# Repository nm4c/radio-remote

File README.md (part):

# RadPi

RadPi puts a two-way radio on the web. A Raspberry Pi sits next to a radio, or carries its own
transceiver on a HAT, and anyone with a browser can listen, talk and run the radio from
anywhere, on a phone or a PC.

- **Remote operation:** receive audio and push-to-talk with low-latency WebRTC audio. Change
  channels or tune frequencies on a radio-style control head (a desk head on wide screens, a
  handheld on phones).
- **Two hardware options:**
  - The **RadPi Control HAT** drives an existing radio through its mic connector. It works with
    most land-mobile and UHF CB radios.
  - The **RadPi SA818 HAT** has a built-in 1 W UHF transceiver, with frequencies, CTCSS/DCS,
    a VFO and signal strength.
- **On-air tools:** selcall (send and decode), audio clips played to air, text to speech in a
  choice of voices (Australian male and female included), recording of the channel, voice
  effects, and TX tone control.
- **AI agent (optional):**
  - It transcribes the channel and recognises who's talking.
  - It learns new voices and names, and keeps notes on people.
  - It can banter on air in a persona and voice you choose, including an Australian one you
    train yourself.
  - The models can run on the Pi, on an AI HAT+ 2, or in the cloud.
- **Several operators, safely:** personal accounts with control or listen-only roles, an audit
  log, and one transmitter at a time. Transmit time-outs drop PTT if a browser goes quiet.
- **Open source:**
  - Software: GPL-3.0.
  - Hardware: CERN-OHL-S. Both HATs are KiCad projects with JLC-ready parts.
  - Mock radio and audio backends let you try it all on a laptop.

There are two hardware modes, set with `radio.type` in `config.yaml`:

| `radio.type` | Hardware | Channels |
|---|---|---|
| `buttons` (default) | An external radio through the **[RadPi Control HAT](pihat/)** (or hand-wired optos, [docs/HARDWARE.md](docs/HARDWARE.md)) | The radio's own channels, stepped with UP/DOWN presses |
| `sa818` | The **[RadPi SA818 HAT](sa818s-hat/)**: a 1 W UHF transceiver on the HAT, no external radio | A frequency/tone list in `config.yaml`, set over the module's serial port, plus direct frequency entry. Shows signal strength (RSSI) |

```
 Browser (phone / PC)                     Raspberry Pi                      Radio  
┌───────────────────┐   WebSocket    ┌──────────────────────┐  GPIO+opto  ┌──────────┐
│ PTT / CH▲▼ / list │◄──────────────►│ server (Python)      │────────────►│ PTT UP DN│
│ mic ─► Opus       │  JSON control  │  - PTT safety timers │  USB audio  │ MIC in   │
│ speaker ◄─ Opus   │◄══════════════►│  - channel tracking  │◄───────────►│ SPK out  │
│                   │ WebRTC (UDP)   │                      │             │          │
└───────────────────┘                └──────────────────────┘             └──────────┘
```

## Features

- Hold-to-talk button (mouse, touch or **Space** key). Mic audio streams to the radio.
- Low-latency audio over WebRTC (Opus over UDP), with automatic fallback to audio over the WebSocket.
  Settings shows the round trip and receive buffer.
- Receive audio with an RX level meter and a BUSY indicator.
- Channel ▲/▼ and jump-to-channel. The Pi presses UP/DOWN the right number of times.
- Channel names are set in config.
- Selcall: send 1-20 digit sequential tone calls from the radio face, and see calls heard on
  the channel. See [Selcall](#selcall).
- Audio clips: upload MP3s (or any audio the browser can play), pick one, and transmit it with
  the radio's Play key. See [Audio clips](#audio-clips).
- Say (off until you switch it on): type something, pick a voice, and the Pi speaks it on air.
  See [Say (text to speech)](#say-text-to-speech).
- Voice effects: Vader, Dalek, Demon, Robot, Giant, Female, Chipmunk and Ghost, switched on
  and off with the radio's P key. See [Voice effects](#voice-effects).
- Recording: the orange button records what the radio hears into 15-minute parts, which join the
  clip list. See [Recording](#recording).
- AI agent (off until you switch it on): transcribes the channel, recognises voices, learns new
  people, and can banter on air in a persona and voice of your choosing. See [AI agent](#ai-agent).
- A radio-style control head: a desk head on wide screens and a portrait handheld on phones.
  See [Control head](#control-head).
- With the RadPi SA818 HAT: frequencies, repeater offsets and CTCSS/DCS per channel, a VFO for any
  frequency in the band, and an RSSI bar on the display.
- Several operators can listen at once. Only one can transmit, and the others see who's on air.
- Personal accounts with **control** (everything) or **listen** (hear only) roles, an audit log of
  who did what, and login lockout. See [Accounts and security](#accounts-and-security).
- Safety features:
  - Server-side transmit time-out (`max_tx_seconds`).
  - PTT drops if the browser goes quiet (network loss, closed tab, phone locked).
  - PTT drops if the browser window loses focus.
  - No channel changes while transmitting.
  - GPIO pins stay low at boot.
- Mock GPIO and mock audio, so you can develop on a laptop without the radio.

## Try it on your laptop (no hardware)

```bash
cd radpi
python3 -m venv .venv && source .venv/bin/activate
pip install -r requirements.txt
cp config.example.yaml config.yaml
#  in config.yaml set: gpio.backend: mock, audio.backend: mock
python -m server.users -c config.yaml add me --role control    # asks for a password
python -m server -c config.yaml
```

Open <http://localhost:8080>. `localhost` counts as secure, so the mic works.
You'll hear a test tone burst every 10 s, and PTT/channel presses show in the server log.
Set `radio.type: sa818` to try the SA818S mode: the mock module answers commands and reports a wandering RSSI.
The mock audio also plays a received selcall (to `selcall.my_id`, or 12345) every 30 s.
Set `audio.backend: sounddevice` to use your laptop's own mic and speakers as a pretend radio.

## Control head

The top of the page is drawn as a radio. Wider screens get a desk control head and phones
(600 px and narrower) get a handheld. Both show the channel, name, frequency, TX with the
time-out countdown, BUSY, RSSI and signal bars.

| Control | Does |
|---|---|
| Channel knob (right on the desk head, the tall one on the handheld) | Picks a channel. The channel shows straight away in amber and is sent once you stop turning. |
| D-pad up / down | One channel up or down |
| Volume knob | Speaker volume, the same as the slider |
| Soft keys | Call (send the selcall number, or open the Selcall panel if none is entered), Play (transmit the picked audio clip; it shows Stop while a clip is on air), Chans (channel list, desk only), Tune (SA818) or Sync (button radios; desk only while clips are on), Setup (Settings) |
| Menu (handheld) | Settings |
| P (desk), P1 (handheld) | Switch the voice effect picked in the Voice effects panel on or off. The display shows FX while it's on. |
| Power (desk), held 1.5 s | Disconnect |
| Orange button (desk: top right; handheld: on top by the antenna) | Record: starts or stops recording received audio. While recording, any other control except the volume knob also stops it (and does nothing else). See [Recording](#recording). |

Knobs turn by dragging or with the mouse wheel. The handheld's top knobs roll with a swipe
across them. A focused knob also takes the arrow keys. PTT stays a separate button (or Space),
because neither head has one on its face.

The artwork is generated. Change `assets/control-head/build_template.py` (desk) or
`build_handheld.py` (handheld), then run them; they need `rsvg-convert` for the PNGs:

```bash
python3 assets/control-head/build_template.py && python3 assets/control-head/build_handheld.py
```

They write the app's SVGs and `radio_config.js` to `web/control-head/`, and PNG layers,
layout JSON and standalone test pages to `assets/control-head/output/`. The input handling,
`web/control-head/control_head.js`, is hand-written and shared by both templates.

## Selcall

Sequential tone calls of 1 to 20 digits, in the CCIR (100 ms tones), ZVEI-1 (70 ms) or EEA (40 ms)
standard (`selcall.standard`). Set `selcall.tone_ms` to run the standard's frequencies at another
tone length, such as CCIR at 50 ms. The decoder still hears calls with longer tones than that.
A digit that repeats the one before it is sent as the repeat tone.

- **Sending:** type the number in the Selcall panel, or tap a preset or an earlier call, then
  press the **Call** soft key. The Pi keys the radio, waits
  `tx_delay_ms` for the transmitter to come up, plays the tones into the mic line and unkeys.
  PTT is locked out while a call goes out, and a call can't start while anyone transmits.
- **Receiving:** the Pi watches the received audio for selcalls. Calls show on the head's bottom
  line, as a notice, and in the panel's list. A call to this station's `selcall.my_id` is
  highlighted and plays a short chime. Sequences shorter than `decode_min_digits` are ignored,
  so speech doesn't set it off. The decoder accepts tones up to about 2% off frequency.

The tones go out through the same audio path as voice, so `audio.tx_gain` and the sound card's
mixer apply (but not the TX tone control below, which would change their levels). Set `selcall.level` so the tones give normal deviation, about the same as speech.
Write selcall numbers in the config in quotes (`my_id: "01234"`), so leading zeros are kept.

## Audio clips

Recordings kept on the Pi and sent on air from the control head: a net opening, an ID, a test
message.

- **Adding:** in the Audio clips panel, press **Upload audio…** and choose one or more files.
  The browser converts each one itself (MP3, M4A, WAV, OGG: anything it can play), to mono at
  the wire rate, trims silence off the ends and uploads it. The Pi needs no audio codecs. Clips
  are limited to `clips.max_seconds` (60 s) and `clips.max_files` (50), and are shared by every
  operator.
- **Sending:** pick a clip, then press the **Play** soft key. The Pi keys the radio, waits
  `tx_delay_ms`, plays the clip and unkeys. While it plays, the key reads **Stop**, and any
  operator can press it to cut the clip off. PTT and selcalls are locked out meanwhile, and a clip
  can't start while anyone transmits. The transmit time-out still applies.
- **Level:** every clip is played with its peak at `clips.level`, so loud and quiet recordings
  go out alike. Like voice, it then goes through `audio.tx_gain` and the sound card's mixer.

The files are kept in `clips.dir` (`/opt/radpi/clips` on an install), as WAV files with
a `clips.json` list. `update.sh` leaves them alone. **Listen** next to a clip plays it in the
browser, where you can also save it. **Rename** gives a clip or recording a new name (up to
40 characters) for everyone; the file on the Pi keeps its ID, so nothing else changes.

## Recording

Press the orange button on the radio (or **Record** in the Audio clips panel) to record the
channel. Press it again to stop. While recording, pressing any other control except the
volume knob also stops it, and that press does nothing else.

- The display shows **REC**, and the panel shows the time so far and who started it.
- **Two modes**, picked with the tick box under the record bar before you start (the orange
  button uses the same setting; `record.mode` sets the default):
  - **Continuous:** everything, silence included.
  - **Only while the channel is active (VOX):** just the overs, back to back with a short gap
    (`vox_gap_ms`, 0.3 s) instead of the silence between them. "Active" means the busy line, or
    the RX level above `audio.busy_threshold_dbfs` without one, or us transmitting. Each over
    keeps `vox_preroll_ms` (0.5 s) from before it started, so the first syllable isn't lost, and
    recording runs on for `vox_hang_ms` (2 s) after it, so short pauses don't chop it up. The bar
    shows how much has been captured.
- **Both sides of the conversation.** While the radio is keyed its receiver is muted, so the
  recording takes what we send instead: voice (after any voice effect), selcalls and clips,
  copied from the sound card output in step with the received audio, at speech level whatever
  `audio.tx_gain` is. Turn this off with `record.include_tx: false`.
- Recordings are split into parts of `record.max_minutes` (15) of audio. When a part is full it
  joins the clip list as "Recording 08 Nov 14:05:00" and the next part starts with no gap.
  Stopping finishes the part in progress. In VOX mode a part is also finished after
  `vox_close_idle_minutes` (10) of quiet, so the overs so far appear in the list.
- It runs on the Pi, so it carries on with no one connected. It also carries on after a restart,
  and a part cut short by a power failure is recovered into the list.
- Storage: about 115 MB an hour. Once recordings pass `record.keep_mb` (2000 MB, about 17
  hours), the oldest are deleted. Uploaded clips are never deleted automatically. Recording
  stops, with a notice, if the disk gets down to `record.min_free_mb`.
- A recording can be played on air like any clip if it fits inside `ptt.max_tx_seconds`.
  Longer ones can't be picked, but you can still listen to and save them.

## Say (text to speech)

Type something in the **Say** panel, pick a voice and press **Say on air** (or Ctrl+Enter). The
Pi turns it into speech, keys the radio, waits `tts.tx_delay_ms` and speaks it, like a clip.
**Listen first** plays it in your own browser only, so you can check a voice or a tricky word
before it goes out. Off by default: set `tts.enabled: true` and list the voices in
`config.yaml` (see the `tts:` section of `config.example.yaml`).

- **Voices:** each one in `tts.voices` has a name for the list, a backend and that backend's
  voice. Mix them freely; the first is the default, and each browser remembers its last pick.

  | Backend | Australian voices | Notes |
  |---|---|---|
  | `azure` (Azure AI Speech) | `en-AU-NatashaNeural` (female), `en-AU-WilliamNeural` (male), and more | Natural sounding. Free tier. Needs `tts.azure.api_key` and `region` (e.g. `australiaeast`) |
  | `google` (Cloud Text-to-Speech) | `en-AU-Neural2-A`/`C` (female), `en-AU-Neural2-B`/`D` (male) | Needs `tts.google.api_key` |
  | `elevenlabs` | any Australian voice from its voice library | The most lifelike; small free tier. Needs `tts.elevenlabs.api_key` |
  | `piper` (offline, on the Pi) | none ready-made: [train your own](docs/voice/README.md) | British and American voices work out of the box. `sudo /opt/radpi/.venv/bin/pip install piper-tts`, then download a voice's `.onnx` and `.onnx.json` |

  The cloud voices need the internet and take about a second; Piper works with no connection.
- **Stopping:** while it speaks, any control operator can press **Stop**. PTT, clips and
  selcalls are locked out meanwhile, and Say can't start while anyone transmits. Text that takes
  longer than `ptt.max_tx_seconds` to say is refused, so split long messages up.
- **Level and words:** speech goes out with its peak at `tts.level`, through the TX tone
  control and `audio.tx_gain`. Add words it says wrong to `tts.pronounce`, spelled the way
  they should sound (`{"Wagga": "Wogga"}`).
- **Records:** each one is in the audit log (who, which voice, the text) and on the head's
  bottom line while it's on air. Listen-only accounts don't see the panel.
- **Keys:** the AI agent's voice (`bot.tts`) uses the same cloud keys if it doesn't have its own.

## Voice effects

Pick an effect in the **Voice effects** panel, then press **P** on the desk head (**P1** on the
handheld) to switch it on or off. The display shows **FX** while it's on, and the bottom line
briefly names the effect. Picking another effect while one is on switches straight to it, even
mid-transmission. Each operator has their own choice.

Every effect rebuilds the voice from scratch rather than just shifting it. The Pi splits your
speech into *what* is said (the shape of the mouth and throat, which carries the words) and *how*
your voice sounds (pitch, roughness, timbre), throws the second part away, and plays the first
through a new synthetic voice. Your own voice doesn't get through; only your timing and
articulation remain. Each effect then sets the new voice's size, pitch and colour:

| Effect | New voice |
|---|---|
| Vader | Bigger tract, 78 Hz, a metallic "mask" echo, light saturation |
| Dalek | Slightly small, near-monotone 95 Hz, through a 30 Hz ring modulator (as on the original) |
| Demon | Huge tract, 58 Hz with an octave-down growl, breath, distortion, a dark room |
| Robot | Monotone 100 Hz with a metallic comb |
| Giant | Big tract, 62 Hz, heavy bass, a large room |
| Female | Shorter tract, 205 Hz following your intonation, breathy |
| Chipmunk | Small tract, 330 Hz |
| Ghost | Whisper only (no pitch), with a long reverb |

The Pi applies the effect to your live voice only. Clips and selcalls go out unchanged, and the TX
tone control below still applies after the effect. Each effect is matched to the dry voice's
loudness and soft-limited, so deviation stays about the same. They add about 35 ms of delay.
Speak clearly: the new voice carries your articulation, and the strongest effects are harder to
understand on a weak signal. Each preset is a few lines in `server/voicefx.py` (warp = tract
size, f0 = pitch, keep = how much intonation survives) if you want to tune them.
Turn the feature off with `voice_fx: enabled: false`.

## AI agent

An optional agent that listens to the channel and can talk back. Turn it on with
`bot: enabled: true` in `config.yaml` (see the `bot:` section of `config.example.yaml`). An
**AI agent** panel then appears in the page. With `enabled: false` (the default) none of it loads
and the panel stays hidden.

Its Python packages (Whisper, the speaker model, Piper and PyTorch) come to well over a gigabyte,
so they're only installed if you ask:

- **New install:** `sudo ./deploy/install.sh --with-ai`.
- **Existing install:** `sudo ./deploy/update.sh --with-ai`. After that, plain `update.sh` keeps
  them up to date. Without the flag they're never downloaded.
- **Removing them:** `sudo ./deploy/update.sh --without-ai` rebuilds the venv without them.

For each over it:

1. Transcribes it: Whisper on the Pi's CPU (`faster_whisper`), or any OpenAI-compatible
   transcription server.
2. Works out who it was: a voiceprint (SpeechBrain ECAPA) compared with the people it knows.
   People you name are **known**. An unfamiliar voice is kept as **Caller N** and recognised next
   time, and becomes **acquainted** once it hears their name. Each person's voiceprint keeps a
   spread of their overs and matches on the closest few, so someone on two different radios is
   still one person. Callers that turn out to have the same voice are merged. When it isn't sure,
   it says so rather than guessing. A handle or name said on air beats the voice match.
   To tune the thresholds (`bot.speaker`): `python -m server.bot people --similar`.
3. Decides whether to say something: an LLM gets the persona, what it knows about the speaker
   (their notes), the last few overs and the new one. It runs on Ollama, on hailo-ollama on the
   AI HAT+ 2 (Pi 5), or on any OpenAI-compatible server. It can also add to the speaker's notes
   and pick up their name.
4. Speaks: Piper offline (your own Australian voice: [docs/voice/README.md](docs/voice/README.md)),
   or Azure, Google or ElevenLabs Australian voices over the internet. With `bot.tones` on, it
   picks a tone for each reply: normal, raised or shout. It also hears when someone is shouting,
   from the over's level against the channel's usual. A raised or shouted reply is faster, higher
   and louder (the cloud voices), and is driven into the mic like someone yelling (every voice).

The panel shows the live transcript with who said what and how sure it is. Control operators can:

- Switch its mode:
  - **Listen**: transcribe and identify only.
  - **Approve**: each reply waits for **Send** or **Discard**.
  - **Auto**: replies go on air by themselves.
- Stop it mid-sentence.
- Name a voice from any over (**Name…**).
- Rename, merge or forget people.

Behaviour comes from the config and the persona prompt, not the code:

- The persona: `bot.persona`. Built in: `banter` (friendly, the default) and `cb` (foul-mouthed, gives as good as it gets), in `server/bot/prompts/`; or a path to your own file.
- When it speaks: `reply_policy` is `llm`, `always` or `addressed`.
- Rate limits: `max_replies_per_hour`, `min_reply_gap_s`. They're off by default.
- What it learns: `learn_anonymous`, `learn_notes`.

The code fixes only the radio mechanics:

- It waits for the channel to be quiet (`reply_gap_ms`) and never keys over anyone.
- Replies are capped at `max_reply_s`, and the server's transmit time-out still applies.
- Any operator can stop it.

Its transmissions go in the audit log as `kind: bot`.

Everything it learns is plain files in `bot.dir`. These can be read, edited and deleted directly:

- `people/people.json`: who it knows.
- `people/<id>.md`: notes on each person.
- `people/<id>.npy`: voiceprints.

The research log is `bot.dir/log/<date>.jsonl`. It records every over: transcript, speaker match
and score, and timings. It records every LLM decision, including the raw answer and silences, and
what happened to each reply (sent, dropped and why, discarded, stopped). With `keep_audio` it also
keeps each over's audio. `retention_days` prunes old logs and audio.

Try it without a radio, on recordings:

```bash
python -m server.bot -c config.yaml enrol --name Dave dave-1.wav dave-2.wav   # seed a known voice
python -m server.bot -c config.yaml replay overs/*.wav          # each file is one over
python -m server.bot -c config.yaml replay --split evening.wav  # cut a long recording into overs
python -m server.bot -c config.yaml people                      # who it knows
```

`replay` runs the full pipeline and writes the replies it would have sent as WAVs (`--out`). Use
`--dir` to keep test runs out of the live agent's memory.

Rough timings on a Pi 5:

| Step | Time |
|---|---|
| Whisper `base.en` | a few seconds per over |
| Speaker match | well under a second |
| A 1.5B model on the AI HAT+ 2 | a few seconds |
| Piper | faster than real time |

So expect roughly 4–10 s from un-key to reply. Mock backends (`backend: mock` for each) let you
try the panel on a laptop.

## TX tone control

Transmitted voice and clips pass through a bass and treble shelf on the Pi, because phone and
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
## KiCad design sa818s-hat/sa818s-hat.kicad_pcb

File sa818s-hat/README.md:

# RadPi SA818 HAT

A Raspberry Pi 4 HAT with a **built-in 1 W UHF FM transceiver**: no external radio. A NiceRF SA818S-U
module (400–480 MHz) is controlled by the Pi over a serial port, with audio through the same
TLV320AIC3104 I2S codec as the [RadPi Control HAT](../pihat/). It's meant for licensed amateur or
experimental use.

| Block | What's on the board |
|---|---|
| Transceiver | SA818S-U, frequency, CTCSS/DCS and squelch set over UART (9600 8N1, GPIO14/15) |
| Harmonic filter | 7th-order low-pass tuned for 400–480 MHz (−3 dB at about 550 MHz): 0.45–0.65 dB loss across the band, 0.62 dB at 477 MHz, return loss better than 22 dB, about −57 dB at the 2nd harmonic of 477 MHz (simulated with the parts' Q, ESR, self-resonance and tolerances). Murata LQW18AN 18 nH 2 % wirewound inductors (lowest-resistance 0603 version), Murata GJM high-Q C0G capacitors (5.6 pF ±0.1 pF, 13 pF ±2 %), all 0402 |
| Antenna | Vertical through-hole SMA (Amphenol 132134-11 footprint: any vertical THT SMA jack with legs on a 5.08 mm square), hand-soldered (not fitted by JLC), right at the filter output; the antenna screws on through the top of the case. Footprint for a 220 nH static-bleed inductor (L6, not fitted) |
| Control | PTT via MOSFET (boots in receive), high/low power via open-drain MOSFET, power-down on GPIO27, busy from the module's AudioON on GPIO23 |
| Audio | Codec headphone out → −30 dB → MIC_IN; AF_OUT → −6 dB → codec input. Direct, no transformers (shared ground). C0G coupling capacitors and thin-film resistors |
| Power | **From the Pi's 5 V only** (power the Pi from its USB-C socket; no input of its own). Module: TPS7A94 ultra-low-noise LDO at 4.2 V, then a ferrite + polymer-tantalum pi-filter. Codec: TPS7A2033 (3.3 V analog) and TPS7A2018 (1.8 V digital core), each from 5 V so the digital core's current pulses stay off the analog rail |
| ID EEPROM | AT24C32D, write-protected by default (R3 pull-up); ground test point TP1 while writing it |

## Schematic

The whole circuit on one page (click to open it full size; part and net names are searchable). Labels
with the same name are connected. Regenerate it with `python3 tools/overview.py` after changing the
schematic.

## GPIO use

| Pin | GPIO | Function |
|---|---|---|
| 8 / 10 | 14 / 15 | UART TX / RX to the module |
| 11 | 17 | PTT (high = transmit) |
| 13 | 27 | Module power: high = on, low = sleep (pulled low at boot) |
| 15 | 22 | Low power: high = 0.5 W, low = 1 W |
| 16 | 23 | Busy: low = signal present (`busy_pin: 23`, `busy_pull_up: true`) |
| 12, 35, 38, 40 / 3, 5 / 37 | 18–21 / 2, 3 / 26 | I2S, I2C and reset for the codec |

The Pi 4's main UART is normally used by Bluetooth. Add `dtoverlay=disable-bt` (or `miniuart-bt`) to
`/boot/firmware/config.txt`.

## Files

| File | |
|---|---|
| `sa818s-hat.kicad_pro` / `.kicad_sch` / `.kicad_pcb` | KiCad project (from KiCad's built-in Raspberry Pi HAT template) |
| `sa818s-hat.kicad_sym`, `sa818s-hat.pretty/` | Project library: SA818S symbol and footprint, codec symbol |
| `docs/schematic.svg` | The full schematic on one page (made by `tools/overview.py`) |
| `tools/` | Generator for the sheets (`build.py`) and netlist check (`verify.py`). Uses the shared code in `../kicadgen/` and the power and codec sheets from `../pihat/tools/kicad/` |

## Before layout

- **Power budget** (official 5.1 V 3 A Pi supply): Pi 4 up to about 1.3 A, module 0.65–0.75 A on transmit at
  high power, codec and the rest under 50 mA: about 2.1 A. Power-hungry USB devices on the Pi can tip it over.
- **SA818S footprint:** pad positions agree between two independent footprints (one derived from LCSC/EasyEDA)
  and the datasheet drawing. Print it 1:1 and check a module against it before ordering.
- **RF layout:** 50 Ω grounded coplanar waveguide from the module's ANT pad through the filter to the SMA,
  short and straight, with ground vias beside every filter capacitor and a solid ground plane under the module.
  Leave room for a shield can over the module and filter.
- **Supplies:** place C38/C39/C40/C45 at the module's VBAT pad (C45, 100 pF, nearest the pin). U7 (TPS7A94):
  C31/C32 at IN and C33/C35 at OUT with their grounds together at U7's GND pin, no vias in between; SNS
  (pin 8) Kelvin to C33; thermal pad to a large ground area (about 0.6 W while transmitting).
- **12 MHz codec clock:** its 37th–39th harmonics are 444, 456 and 468 MHz (and 432 MHz). Keep Y1 and the
  MCLK trace (R16, 100 Ω to slow the edges) away from the module and the RF path, with ground pour around them.
  Avoid channels within a few kHz of those frequencies. If they're audible on receive, fit the shield can.
- **L6 (not fitted):** before fitting, measure U6 pin 12 for DC with the module receiving and transmitting into a
  dummy load. Fit it only if it reads 0 V.
- **Check harmonics** on a spectrum analyser after the first build, before connecting an antenna.
- **Frequency range:** the module covers 400–480 MHz (the SA818S-CE is the same module with CE-RED certification). NiceRF only promises power flat within 1 dB up to 470 MHz, so measure the output at your frequency.

## Software

Set `radio.type: sa818` in `config.yaml` (see `config.example.yaml`):

- `channel.list`: name, frequency, optional `tx_freq` for repeaters, `tone` (CTCSS Hz or DCS `D023N`),
  and per-channel bandwidth, squelch or low power.
- The web app shows the frequency and tones, an RSSI bar, and a box to tune any frequency in `sa818.band` (the VFO).
- At start-up the server wakes the module (PD), sets volume, audio filters and tail tone, then the channel.
  If the module stops answering, operators see the error, PTT is refused, and the server retries every 5 s.
- `gpio.busy_pin: 23` uses the module's AudioON as the BUSY indicator.
- RSSI is the module's raw 0–255 reading in 1 dB steps. Set `sa818.rssi_offset_db` after checking it against a
  known signal to show dBm.

Pi 4 set-up: `dtoverlay=disable-bt` in `/boot/firmware/config.txt`, the serial console off and the serial
hardware on (`raspi-config` → Interface Options → Serial Port), then reboot. The installer adds the service user
to `dialout` for `/dev/serial0`.

## Licence

Hardware: CERN-OHL-S v2 (see [`LICENSE`](LICENSE)). The generator scripts are GPL-3.0-or-later (see the
repository root).

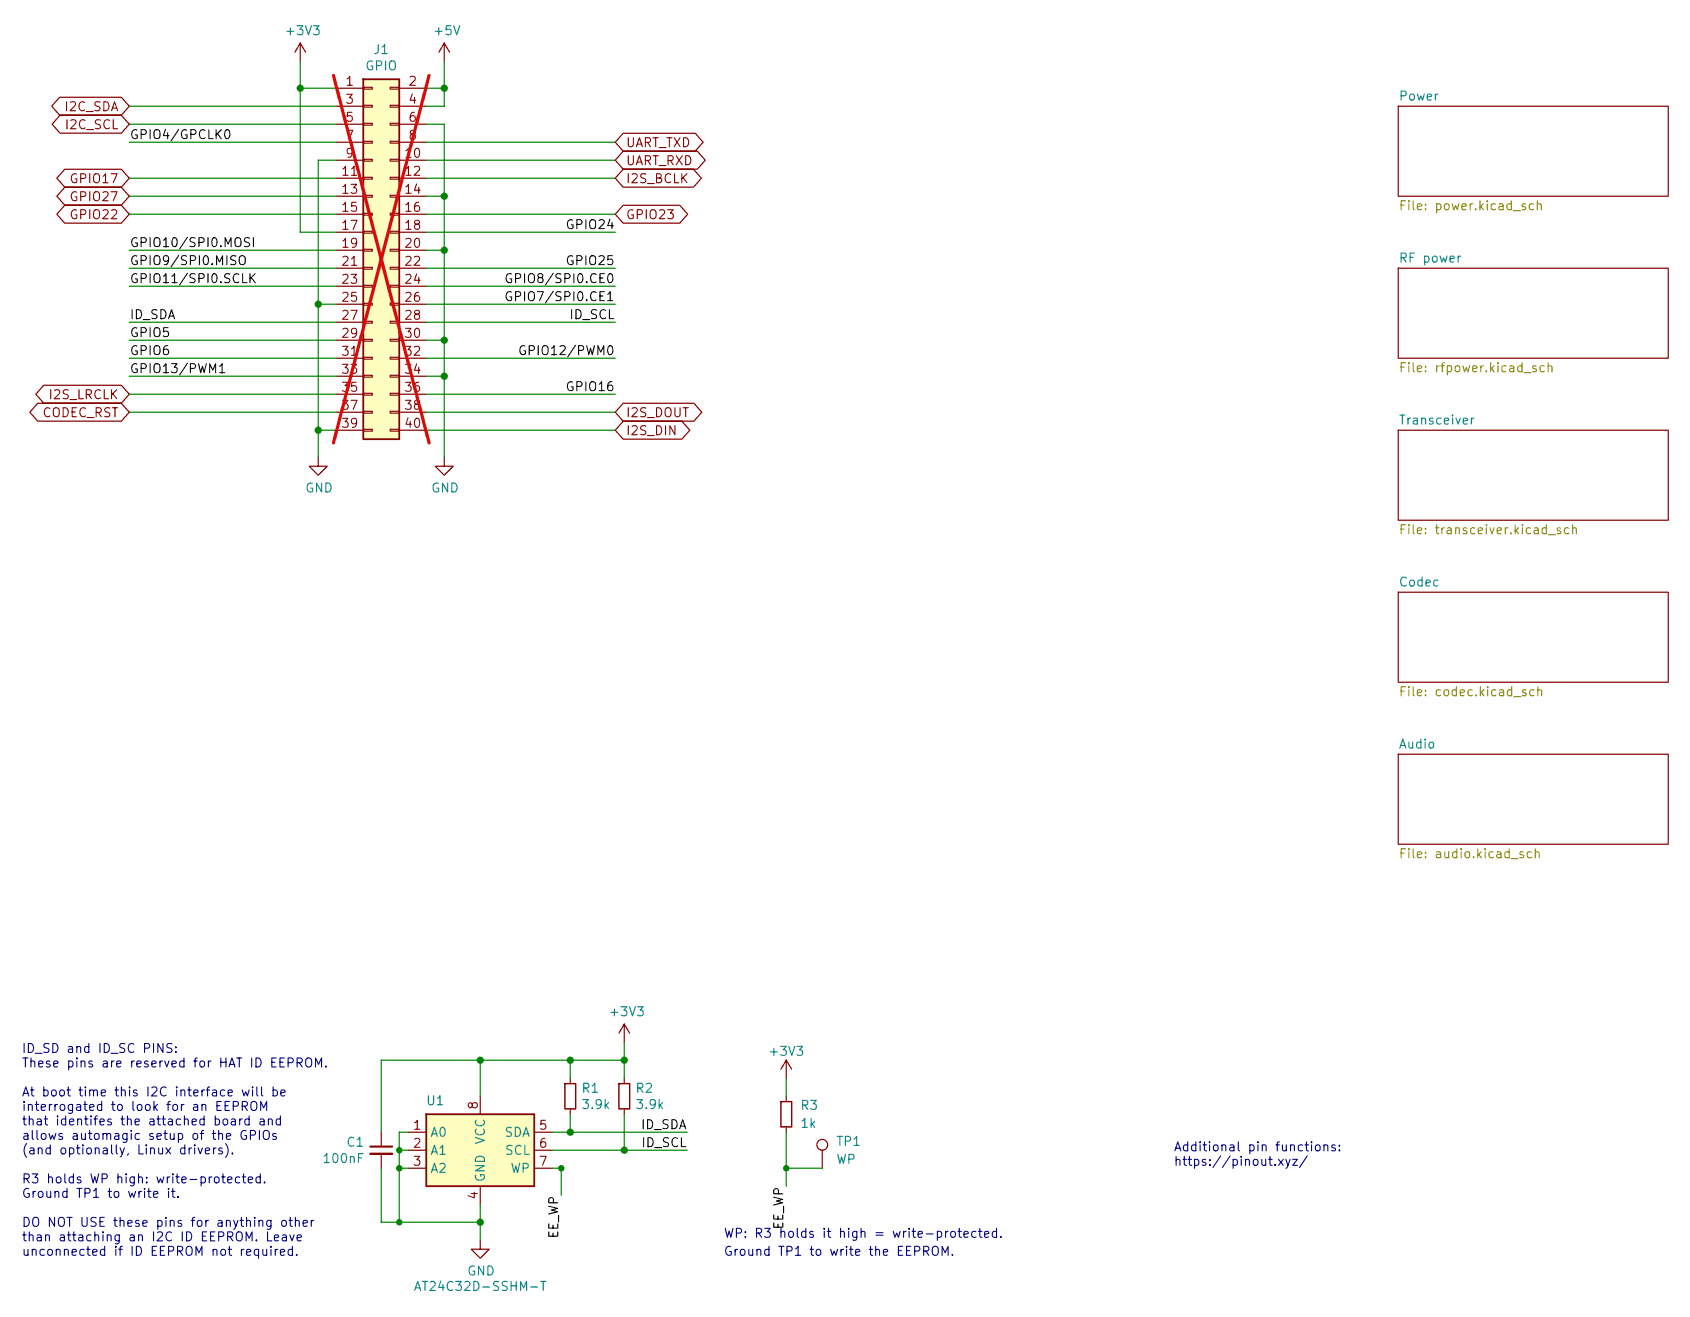
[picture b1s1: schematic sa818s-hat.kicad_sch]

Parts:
C1: 100nF; C_0603_1608Metric; LCSC C14663
J1: GPIO; PinSocket_2x20_P2.54mm_Vertical; LCSC C2977589; not fitted
R1, R2: 3.9k; R_0603_1608Metric; LCSC C23018
R3: 1k; R_0603_1608Metric; LCSC C21190
TP1: WP; TestPoint_Pad_D1.5mm
U1: AT24C32D-SSHM-T; SOIC-8_3.9x4.9mm_P1.27mm; LCSC C60583

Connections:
+3V3: C1.1, J1.1, J1.17, R1.1, R2.1, R3.1, U1.8 (VCC); also elsewhere on the board
+5V: J1.2, J1.4; also elsewhere on the board
/EE_WP: R3.2, TP1.1 (1_1), U1.7 (WP)
/GPIO4/GPCLK0: J1.7
/GPIO5: J1.29
/GPIO6: J1.31
/GPIO7/SPI0.CE1: J1.26
/GPIO8/SPI0.CE0: J1.24
/GPIO9/SPI0.MISO: J1.21
/GPIO10/SPI0.MOSI: J1.19
/GPIO11/SPI0.SCLK: J1.23
/GPIO12/PWM0: J1.32
/GPIO13/PWM1: J1.33
/GPIO16: J1.36
/GPIO24: J1.18
/GPIO25: J1.22
/ID_SCL: J1.28, R2.2, U1.6 (SCL)
/ID_SDA: J1.27, R1.2, U1.5 (SDA)
CODEC_RST: J1.37; also elsewhere on the board
GND: C1.2, J1.6, J1.9, J1.14, J1.20, J1.25, J1.30, J1.34, J1.39, U1.1 (A0), U1.2 (A1), U1.3 (A2), U1.4 (GND); also elsewhere on the board
GPIO17: J1.11; also elsewhere on the board
GPIO22: J1.15; also elsewhere on the board
GPIO23: J1.16; also elsewhere on the board
GPIO27: J1.13; also elsewhere on the board
I2C_SCL: J1.5; also elsewhere on the board
I2C_SDA: J1.3; also elsewhere on the board
I2S_BCLK: J1.12; also elsewhere on the board
I2S_DIN: J1.40; also elsewhere on the board
I2S_DOUT: J1.38; also elsewhere on the board
I2S_LRCLK: J1.35; also elsewhere on the board
UART_RXD: J1.10; also elsewhere on the board
UART_TXD: J1.8; also elsewhere on the board

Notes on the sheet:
Additional pin functions: https://pinout.xyz/
ID_SD and ID_SC PINS: These pins are reserved for HAT ID EEPROM. At boot time this I2C interface will be interrogated to look for an EEPROM that identifes the attached board and allows automagic setup of the GPIOs (and optionally, Linux drivers). R3 holds WP high: write-protected. Ground TP1 to wri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
WP: R3 holds it high = write-protected.
Ground TP1 to write the EEPROM.

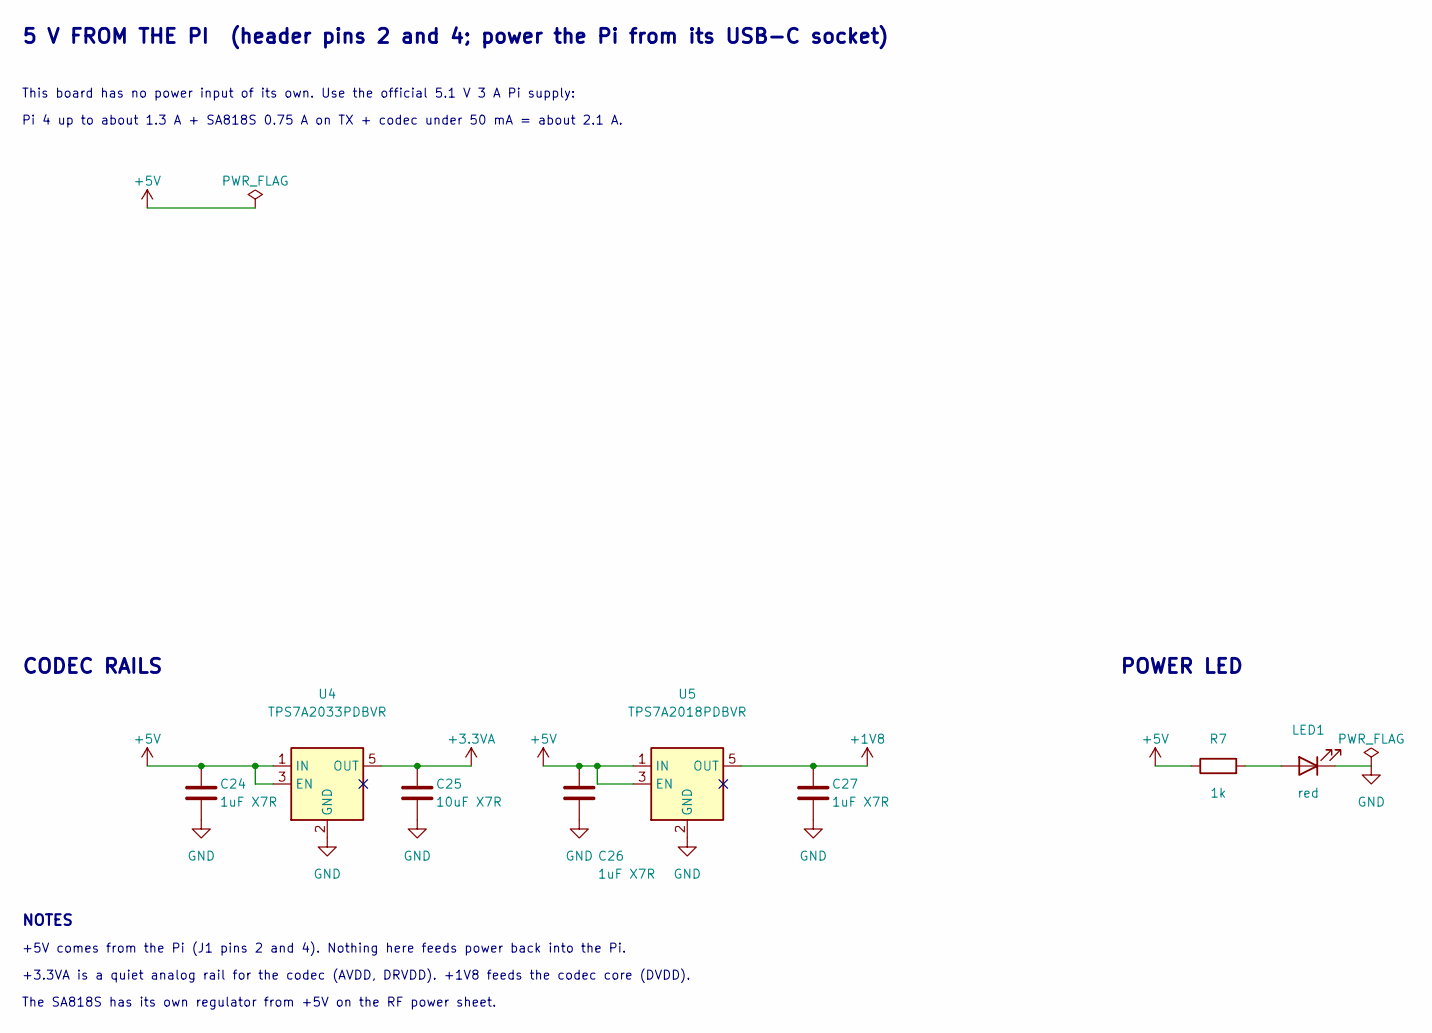
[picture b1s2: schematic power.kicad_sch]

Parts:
C24, C26, C27: 1uF X7R; C_0603_1608Metric; LCSC C29936
C25: 10uF X7R; C_0805_2012Metric; LCSC C95841
LED1: red; LED_0603_1608Metric; LCSC C2286
R7: 1k; R_0603_1608Metric; LCSC C21190
U4: TPS7A2033PDBVR; SOT-23-5; LCSC C2862740
U5: TPS7A2018PDBVR; SOT-23-5; LCSC C963430

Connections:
+1V8: C27.1, U5.5 (OUT); also elsewhere on the board
+3.3VA: C25.1, U4.5 (OUT); also elsewhere on the board
+5V: C24.1, C26.1, R7.1, U4.1 (IN), U4.3 (EN), U5.1 (IN), U5.3 (EN); also elsewhere on the board
GND: C24.2, C25.2, C26.2, C27.2, LED1.1 (K), U4.2 (GND), U5.2 (GND); also elsewhere on the board
unnamed: LED1.2 (A), R7.2

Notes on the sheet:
5 V FROM THE PI (header pins 2 and 4; power the Pi from its USB-C socket)
This board has no power input of its own. Use the official 5.1 V 3 A Pi supply:
Pi 4 up to about 1.3 A + SA818S 0.75 A on TX + codec under 50 mA = about 2.1 A.
CODEC RAILS
POWER LED
NOTES
+5V comes from the Pi (J1 pins 2 and 4). Nothing here feeds power back into the Pi.
+3.3VA is a quiet analog rail for the codec (AVDD, DRVDD). +1V8 feeds the codec core (DVDD).
The SA818S has its own regulator from +5V on the RF power sheet.

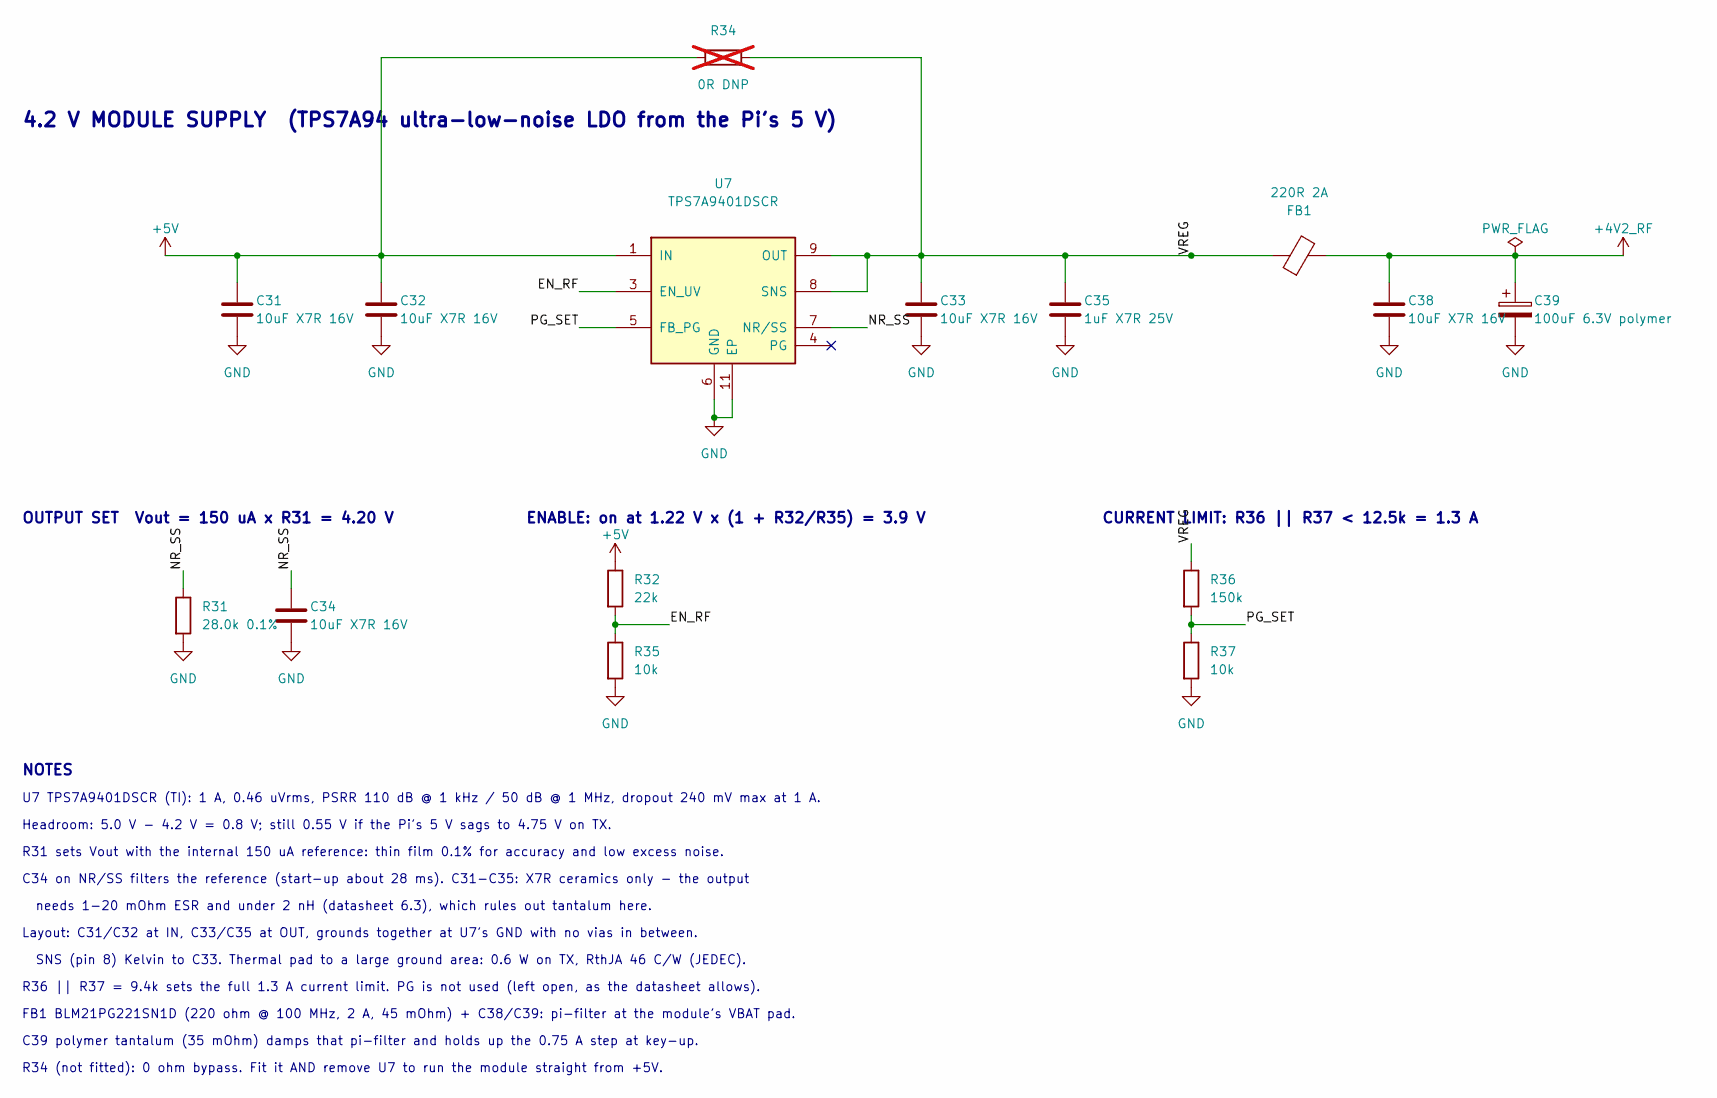
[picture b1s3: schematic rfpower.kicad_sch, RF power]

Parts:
C31, C32, C33, C34, C38: 10uF X7R 16V; C_0805_2012Metric; LCSC C95841
C35: 1uF X7R 25V; C_0603_1608Metric; LCSC C29936
C39: 100uF 6.3V polymer; CP_EIA-3528-21_Kemet-B; MPN Panasonic 6TPE100MAZB (POSCAP, 35 mOhm); LCSC C79109
FB1: 220R 2A; L_0805_2012Metric; LCSC C85840
R31: 28.0k 0.1%; R_0603_1608Metric; MPN FH TD03G2802BT (thin film, 0.1%, 25 ppm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; LCSC C667083
R32: 22k; R_0603_1608Metric; LCSC C31850
R34: 0R DNP; R_1206_3216Metric; not fitted
R35, R37: 10k; R_0603_1608Metric; LCSC C25804
R36: 150k; R_0603_1608Metric; LCSC C22807
U7: TPS7A9401DSCR; Texas_DSC0010J_ThermalVias; LCSC C5220127

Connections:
+4V2_RF: C38.1, C39.1, FB1.2; also elsewhere on the board
+5V: C31.1, C32.1, R32.1, R34.1, U7.1 (IN), U7.2 (IN); also elsewhere on the board
/RF power/EN_RF: R32.2, R35.1, U7.3 (EN_UV)
/RF power/NR_SS: C34.1, R31.1, U7.7 (NR/SS)
/RF power/PG_SET: R36.2, R37.1, U7.5 (FB_PG)
/RF power/VREG: C33.1, C35.1, FB1.1, R34.2, R36.1, U7.8 (SNS), U7.9 (OUT), U7.10 (OUT)
GND: C31.2, C32.2, C33.2, C34.2, C35.2, C38.2, C39.2, R31.2, R35.2, R37.2, U7.6 (GND), U7.11 (EP); also elsewhere on the board

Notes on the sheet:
4.2 V MODULE SUPPLY (TPS7A94 ultra-low-noise LDO from the Pi's 5 V)
OUTPUT SET Vout = 150 uA x R31 = 4.20 V
ENABLE: on at 1.22 V x (1 + R32/R35) = 3.9 V
CURRENT LIMIT: R36 || R37 < 12.5k = 1.3 A
NOTES
U7 TPS7A9401DSCR (TI): 1 A, 0.46 uVrms, PSRR 110 dB @ 1 kHz / 50 dB @ 1 MHz, dropout 240 mV max at 1 A.
Headroom: 5.0 V - 4.2 V = 0.8 V; still 0.55 V if the Pi's 5 V sags to 4.75 V on TX.
R31 sets Vout with the internal 150 uA reference: thin film 0.1% for accuracy and low excess noise.
C34 on NR/SS filters the reference (start-up about 28 ms). C31-C35: X7R ceramics only - the output
needs 1-20 mOhm ESR and under 2 nH (datasheet 6.3), which rules out tantalum here.
Layout: C31/C32 at IN, C33/C35 at OUT, grounds together at U7's GND with no vias in between.
SNS (pin 8) Kelvin to C33. Thermal pad to a large ground area: 0.6 W on TX, RthJA 46 C/W (JEDEC).
R36 || R37 = 9.4k sets the full 1.3 A current limit. PG is not used (left open, as the datasheet allows).
FB1 BLM21PG221SN1D (220 ohm @ 100 MHz, 2 A, 45 mOhm) + C38/C39: pi-filter at the module's VBAT pad.
C39 polymer tantalum (35 mOhm) damps that pi-filter and holds up the 0.75 A step at key-up.
R34 (not fitted): 0 ohm bypass. Fit it AND remove U7 to run the module straight from +5V.

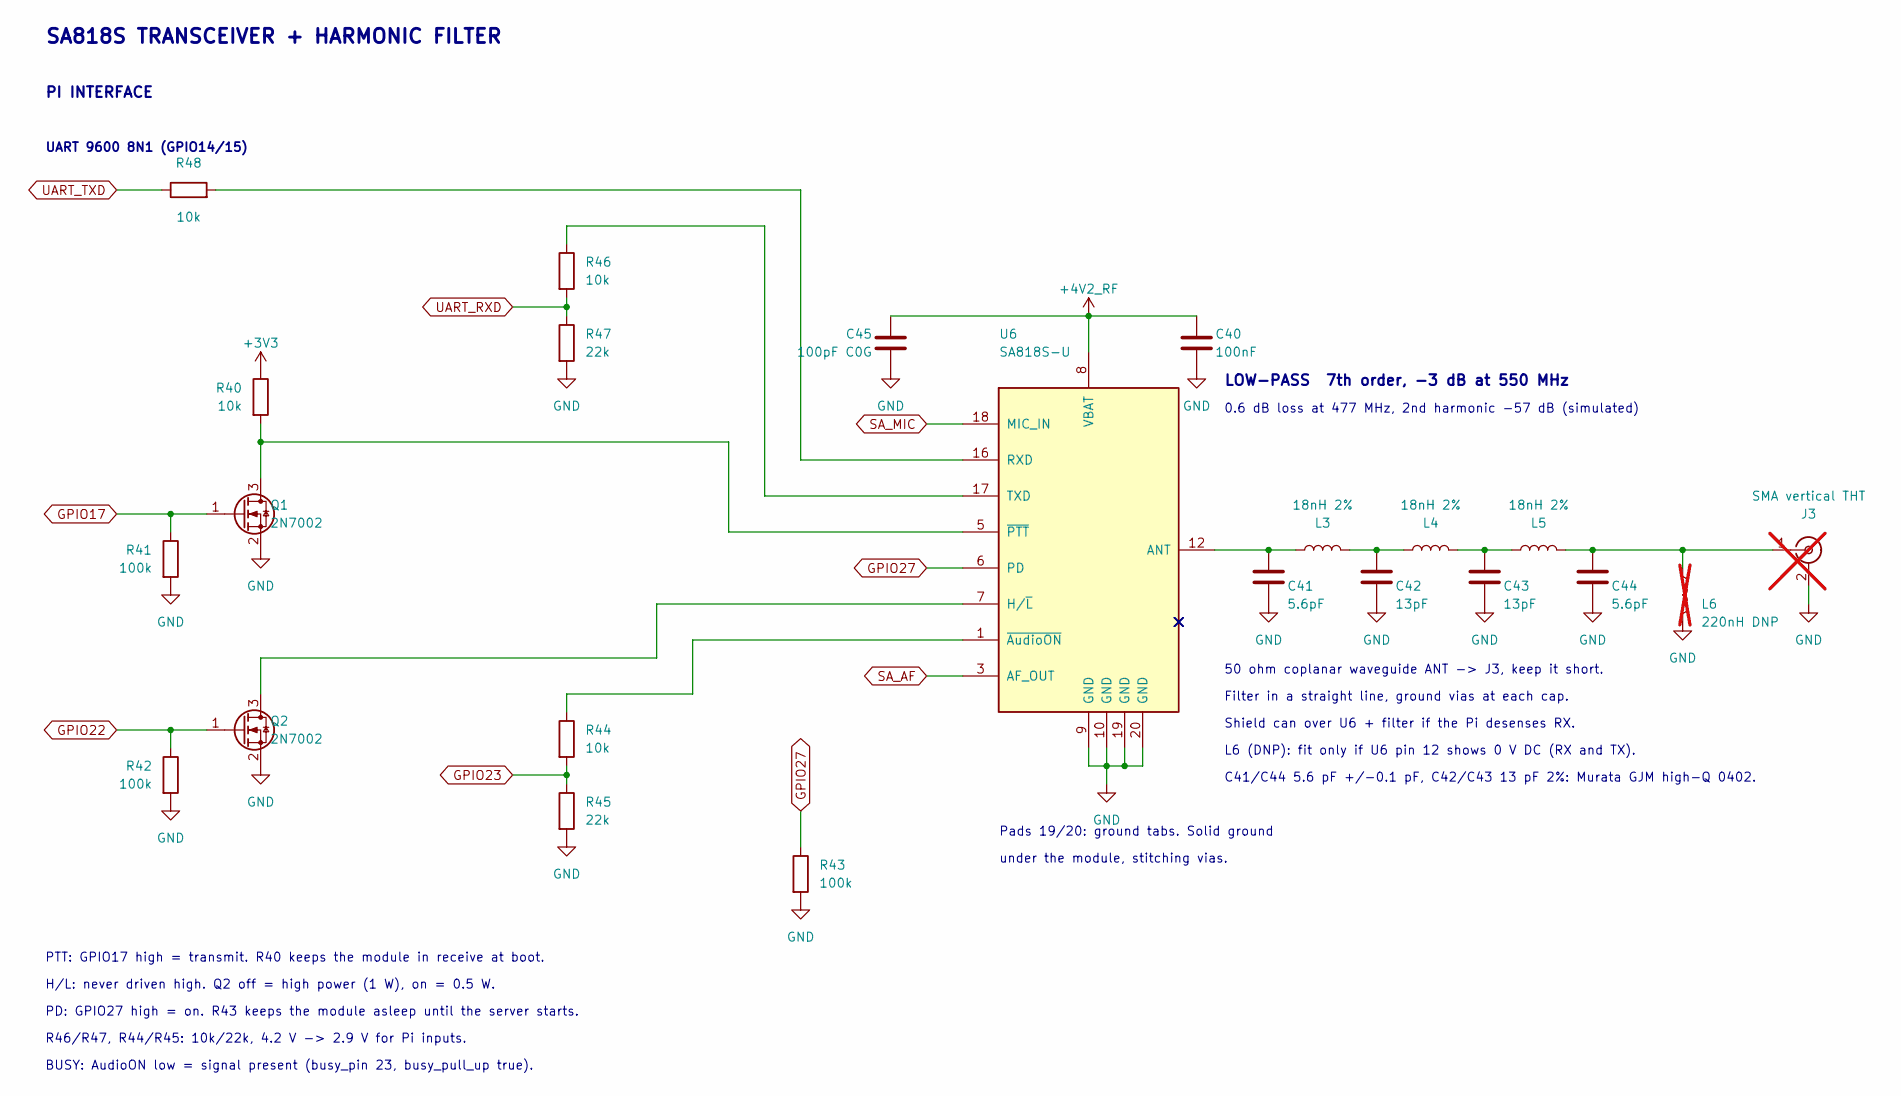
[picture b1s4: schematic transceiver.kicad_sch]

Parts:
C40: 100nF; C_0603_1608Metric; LCSC C14663
C41, C44: 5.6pF; C_0402_1005Metric; LCSC C161329
C42, C43: 13pF; C_0402_1005Metric; LCSC C2167421
C45: 100pF C0G; C_0603_1608Metric; LCSC C14858
J3: SMA vertical THT; SMA_Amphenol_132134-11_Vertical; MPN Amphenol RF 132134-11, or any vertical 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; not fitted
L3, L4, L5: 18nH 2%; L_0603_1608Metric; LCSC C1330613
L6: 220nH DNP; L_0603_1608Metric; MPN Coilcraft 0603CS-R22XGLU (220 nH 2%, SR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; not fitted
Q1, Q2: 2N7002; SOT-23; LCSC C8545
R40, R44, R46, R48: 10k; R_0603_1608Metric; LCSC C25804
R41, R42, R43: 100k; R_0603_1608Metric; LCSC C25803
R45, R47: 22k; R_0603_1608Metric; LCSC C31850
U6: SA818S-U; NiceRF_SA818S; LCSC C3001549

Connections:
+3V3: R40.1; also elsewhere on the board
+4V2_RF: C40.1, C45.1, U6.8 (VBAT); also elsewhere on the board
GND: C40.2, C41.2, C42.2, C43.2, C44.2, C45.2, J3.2 (Ext), L6.2, Q1.2 (S), Q2.2 (S), R41.2, R42.2, R43.2, R45.2, R47.2, U6.9 (GND), U6.10 (GND), U6.19 (GND), U6.20 (GND); also elsewhere on the board
GPIO17: Q1.1 (G), R41.1; also elsewhere on the board
GPIO22: Q2.1 (G), R42.1; also elsewhere on the board
GPIO23: R44.2, R45.1; also elsewhere on the board
GPIO27: R43.1, U6.6 (PD); also elsewhere on the board
unnamed: C42.1, L3.2, L4.1
unnamed: C43.1, L4.2, L5.1
unnamed: C44.1, J3.1 (In), L5.2, L6.1
unnamed: Q1.3 (D), R40.2, U6.5 (~PTT)
unnamed: Q2.3 (D), U6.7 (H/~L)
unnamed: C41.1, L3.1, U6.12 (ANT)
unnamed: R48.2, U6.16 (RXD)
unnamed: R46.1, U6.17 (TXD)
unnamed: R44.1, U6.1 (~AudioON)
SA_AF: U6.3 (AF_OUT); also elsewhere on the board
SA_MIC: U6.18 (MIC_IN); also elsewhere on the board
UART_RXD: R46.2, R47.1; also elsewhere on the board
UART_TXD: R48.1; also elsewhere on the board

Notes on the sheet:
SA818S TRANSCEIVER + HARMONIC FILTER
Pads 19/20: ground tabs. Solid ground
under the module, stitching vias.
LOW-PASS 7th order, -3 dB at 550 MHz
0.6 dB loss at 477 MHz, 2nd harmonic -57 dB (simulated)
50 ohm coplanar waveguide ANT -> J3, keep it short.
Filter in a straight line, ground vias at each cap.
Shield can over U6 + filter if the Pi desenses RX.
L6 (DNP): fit only if U6 pin 12 shows 0 V DC (RX and TX).
C41/C44 5.6 pF +/-0.1 pF, C42/C43 13 pF 2%: Murata GJM high-Q 0402.
PI INTERFACE
UART 9600 8N1 (GPIO14/15)
PTT: GPIO17 high = transmit. R40 keeps the module in receive at boot.
H/L: never driven high. Q2 off = high power (1 W), on = 0.5 W.
PD: GPIO27 high = on. R43 keeps the module asleep until the server starts.
R46/R47, R44/R45: 10k/22k, 4.2 V -> 2.9 V for Pi inputs.
BUSY: AudioON low = signal present (busy_pin 23, busy_pull_up true).

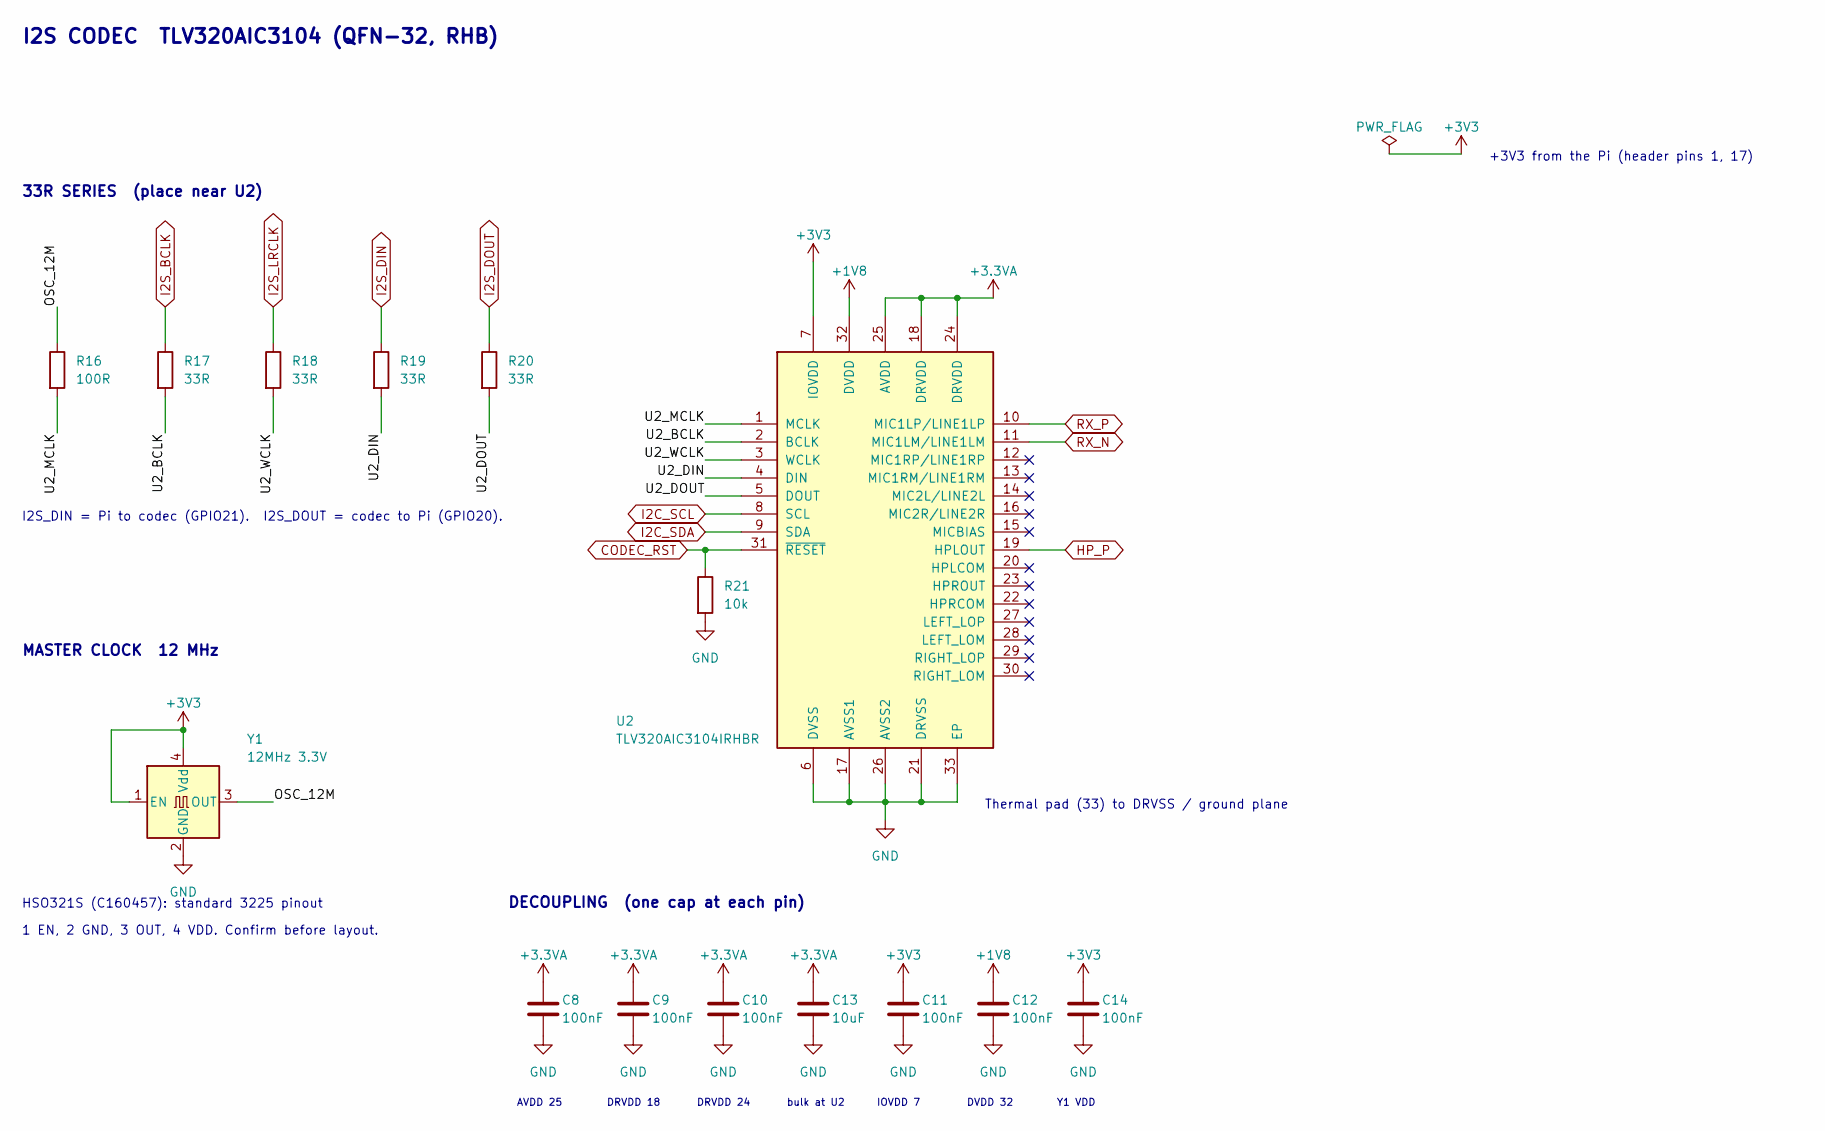
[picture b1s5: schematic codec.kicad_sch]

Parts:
C8, C9, C10, C11, C12, C14: 100nF; C_0603_1608Metric; LCSC C14663
C13: 10uF; C_0805_2012Metric; LCSC C95841
R16: 100R; R_0603_1608Metric; LCSC C22775
R17, R18, R19, R20: 33R; R_0603_1608Metric; LCSC C23140
R21: 10k; R_0603_1608Metric; LCSC C25804
U2: TLV320AIC3104IRHBR; QFN-32-1EP_5x5mm_P0.5mm_EP3.45x3.45mm; LCSC C181753
Y1: 12MHz 3.3V; Oscillator_SMD_Abracon_ASE-4Pin_3.2x2.5mm; LCSC C160457

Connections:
+1V8: C12.1, U2.32 (DVDD); also elsewhere on the board
+3.3VA: C8.1, C9.1, C10.1, C13.1, U2.18 (DRVDD), U2.24 (DRVDD), U2.25 (AVDD); also elsewhere on the board
+3V3: C11.1, C14.1, U2.7 (IOVDD), Y1.1 (EN), Y1.4 (Vdd); also elsewhere on the board
/Codec/OSC_12M: R16.1, Y1.3 (OUT)
/Codec/U2_BCLK: R17.2, U2.2 (BCLK)
/Codec/U2_DIN: R19.2, U2.4 (DIN)
/Codec/U2_DOUT: R20.2, U2.5 (DOUT)
/Codec/U2_MCLK: R16.2, U2.1 (MCLK)
/Codec/U2_WCLK: R18.2, U2.3 (WCLK)
CODEC_RST: R21.1, U2.31 (~RESET); also elsewhere on the board
GND: C8.2, C9.2, C10.2, C11.2, C12.2, C13.2, C14.2, R21.2, U2.6 (DVSS), U2.17 (AVSS1), U2.21 (DRVSS), U2.26 (AVSS2), U2.33 (EP), Y1.2 (GND); also elsewhere on the board
HP_P: U2.19 (HPLOUT); also elsewhere on the board
I2C_SCL: U2.8 (SCL); also elsewhere on the board
I2C_SDA: U2.9 (SDA); also elsewhere on the board
I2S_BCLK: R17.1; also elsewhere on the board
I2S_DIN: R19.1; also elsewhere on the board
I2S_DOUT: R20.1; also elsewhere on the board
I2S_LRCLK: R18.1; also elsewhere on the board
RX_N: U2.11 (MIC1LM/LINE1LM); also elsewhere on the board
RX_P: U2.10 (MIC1LP/LINE1LP); also elsewhere on the board

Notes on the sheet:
I2S CODEC TLV320AIC3104 (QFN-32, RHB)
Thermal pad (33) to DRVSS / ground plane
33R SERIES (place near U2)
I2S_DIN = Pi to codec (GPIO21). I2S_DOUT = codec to Pi (GPIO20).
MASTER CLOCK 12 MHz
HSO321S (C160457): standard 3225 pinout
1 EN, 2 GND, 3 OUT, 4 VDD. Confirm before layout.
DECOUPLING (one cap at each pin)
AVDD 25
DRVDD 18
DRVDD 24
bulk at U2
IOVDD 7
DVDD 32
Y1 VDD
+3V3 from the Pi (header pins 1, 17)

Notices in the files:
README.md:
This project is open source and share-alike: you can use, modify, build and sell it,
but anything you distribute that's based on it must be shared under the same terms.
Part | Licence | File
Software: `server/`, `web/`, `assets/control-head/`, `deploy/`, `kicadgen/`, `pihat/tools/`, `sa818s-hat/tools/`, `pihat/docs/schematic/*.py` | GNU GPL v3.0 or later | [`LICENSE`](LICENSE)
Hardware: the KiCad projects in `pihat/` and `sa818s-hat/` (schematics, PCB, symbols, footprints), `pihat/docs/` | CERN-OHL-S v2 | [`pihat/LICENSE`](pihat/LICENSE), [`sa818s-hat/LICENSE`](sa818
